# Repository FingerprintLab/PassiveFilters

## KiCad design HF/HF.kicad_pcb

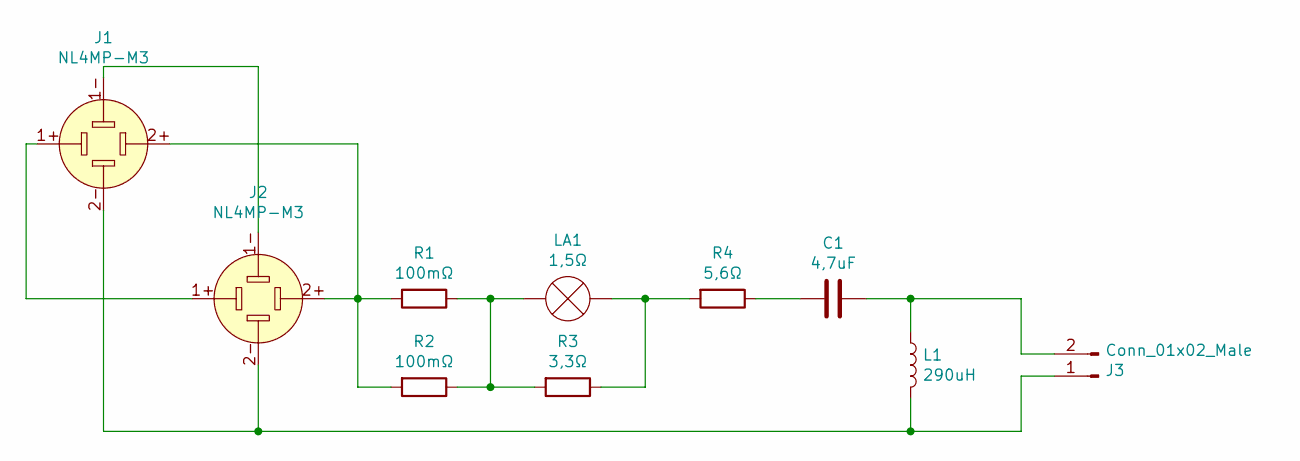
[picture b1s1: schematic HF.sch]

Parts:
C1: 4,7uF; C_Rect_L26.5mm_W8.5mm_P22.50mm_MKS4
J1, J2: NL4MP-M3; NL4MP-M3_double_left
J3: Conn_01x02_Male; Faston_DUAL_01x02_P5.08mm_D5.08mm
L1: 290uH; inductor_40mm
LA1: 1,5Ω; lamp
R1, R2: 100mΩ; ptc_7.2mm_larger
R3: 3,3Ω; resistor_P27.50mm
R4: 5,6Ω; resistor_P27.50mm

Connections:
unnamed: C1.1, J3.2, L1.1
unnamed: C1.2, R4.1
unnamed: J1.1+, J2.1+
unnamed: J1.1-, J2.1-
unnamed: J1.2+, J2.2+, R1.2, R2.2
unnamed: J1.2-, J2.2-, J3.1, L1.2
unnamed: LA1.1 (-), R1.1, R2.1, R3.2
unnamed: LA1.2 (+), R3.1, R4.2

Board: 2 copper layers, 10 parts (1 on the bottom side), 8 nets, no tracks yet.

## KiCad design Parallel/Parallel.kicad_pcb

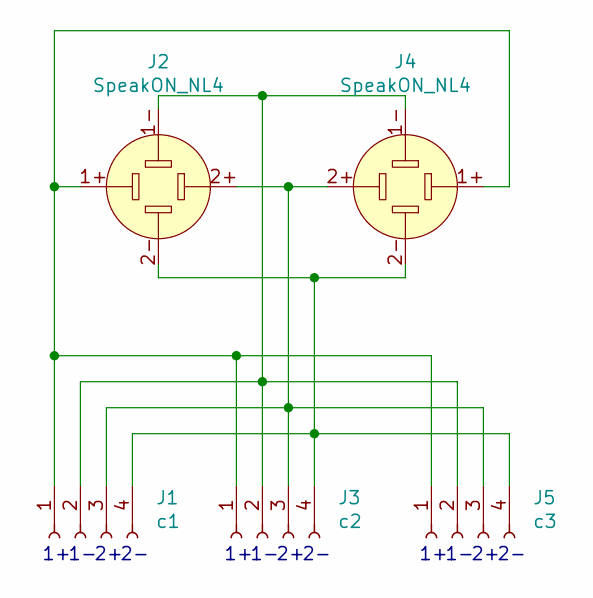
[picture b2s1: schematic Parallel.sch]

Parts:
J1: c1; JST_VH_B4PS-VH_1x04_P3.96mm_Horizontal
J2, J4: SpeakON_NL4; NL4MP-M3
J3: c2; Faston_01x04_P5.08mm_D5.08mm
J5: c3; Phoenix_ZFKDSA_2,5_5,08_4

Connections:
unnamed: J1.1, J2.1+, J3.1, J4.1+, J5.1
unnamed: J1.2, J2.1-, J3.2, J4.1-, J5.2
unnamed: J1.3, J2.2+, J3.3, J4.2+, J5.3
unnamed: J1.4, J2.2-, J3.4, J4.2-, J5.4

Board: 2 copper layers, 5 parts (0 on the bottom side), 4 nets, no tracks yet.

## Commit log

2021-05-17 added everything but the inductor
2021-05-18 inductor added
2021-05-18 updated speakON footprint
2021-06-17 changes from Trello
2021-06-29 added parallel board
